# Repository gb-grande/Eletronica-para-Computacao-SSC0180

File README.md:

# SSC0180 - Eletrônica para Computação

Esse repo reúne os dois trabalhos desenvolvidos para a disciplina de Eletrônica para Computação - SSC0180, ministrada pelo professor Eduardo do Valle Simoes no ICMC.

Membros do grupo:

- Gustavo Bhering Grande - 12542780
- Joao Pedro Hamata - 13672001
- Lucas Oliveira Castro - 13695059
- Rafael de Almeida - 11872028

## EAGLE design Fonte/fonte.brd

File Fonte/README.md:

# FonteEletronica
Este trabalho, referente à disciplina Eletrônica para Computação(ICMC-USP), consiste no projeto e montagem de uma fonte de tensão ajustável entre 3V a 12V com capacidade de 100mA.

Adotou-se como parametros da entrada: Corrente alternada com 127V de tensao e 60Hz de frequencia.

| Apresentação da Fonte | Cálculo do Ripple |
| --- | --- |
| <video src="https://user-images.githubusercontent.com/24720405/178084118-f01fbc68-67f3-4e2c-8ba8-4f21347edacc.mp4" style="max-width: 730px;"></video> | <video src="https://user-images.githubusercontent.com/24720405/178084461-28b8bc12-fb25-4542-be41-ac9ad6f14883.mp4" style="max-width: 730px;"></video> |

| Componente | Preço |
| --- | --- |
| Transformador | R$28,99 |
| Diodo 1n4007 x4 | R$0,20 * 4 = R$0,80 |
| Capacitor 680uF 25v | R$5,78 |
| Resistor 1kΩ | R$0,07 |
| Resistor 750Ω | R$0,07 |
| Resistor 2k2Ω | R$0,07 |
| Potenciômetro Linear 5kΩ | R$7,00 |
| Diodo Zener 13v | R$0,48 |
| transistor NPN BC337-40 | R$0,69 |
| LED | R$0,50 |
| ***TOTAL*** | ***R$44,45*** |

*Componentes comprados na Ca&Ma em São Carlos, 28/06/2022

## Ficha Tecnica
### Transformador: 
Componente elétrico responsável por trasformar a tensão elétrica de entrada em valores mais adequados para uma determinada aplicação, utilizando-se de bobinas e dos princípios eletromagnéticos da Lei de Faraday-Lenz. No projeto, optou-se por um transformador comercial capaz de modificar uma entrada de 127V para aproximadamente 24v.
### Diodos:
Componentes eletricos com a caracteristica de selecionar um sentido unico para a passagem de corrente eletrica. No projeto, sao utilizados na construcao de uma ponte de diodos, dispositivo retificador de tensao por possibilitar o aproveitamento de ambos os ciclos da corrente alternada de origem.
### Resistores:
Componentes eletricos dotados de valores fixos de resistencia responsáveis por garantir a manutencao da corrente no circuito em valores adequados para o funcionamento adequado de cada um dos componentes presentes no circuito.
### Capacitor:
Componente elétrico capaz de armazenar pequenas quantidades de cargas elétricas, fornecendo corrente continua caso a tensão interna encontre-se superior à externa. Para obter um ripple inferior a 10%, seria necessário um capacitor de pelo menos 370uF (explicação no vídeo). No projeto, usamos um de 680uF.
### Potenciômetro:
Componente elétrico dotado de resistência variável, ou seja, capaz de regular a passagem de corrente e consequentemente modificar os valores de tensao do circuito. No projeto, foi utilizado para possibilitar a selecao dos valores de tensao entre 3V a 12V,  conforme descrito nas especificacoes.
### Diodo Zener:
Variacao do diodo tradicional caracterizado por permitir corrente eletrica somente sob a influencia de tensao superior a sua tensao de trabalho especificada pelo fabricante, limitando assim a voltagem maxima permitida pelo circuito. No projeto, foi utilizado para garantir valores de tensao maxima inferiores a 13V, com um espaço para erros do máximo de 12V.
### Transistor:
Componente elétrico capaz de trocar ou amplificar sinais e potencia eletrica. No projeto, foi utilizado na regulagem da corrente eletrica no circuito, para evitar desperdício de corrente no Diodo Zener.

## Funcionamento:
### Transformacao:
Nesta etapa, os sinais eletricos da entrada(corrente alternada com 127V de tensao e 60Hz de frequencia) tem sua DDP reduzida pelo transformador para valores proximos a 24V, sendo mantidas as demais caracteristicas de onda.
### Retificacao:
Nesta etapa, os sinais eletricos em corrente alternada(provenientes da etapa de transformacao) sao retificados para um sinal contiuamente positivo pela acao da ponte de diodos. Nesta estrutura, a disposicao geometrica dos diodos no circuito ora permite ora bloqueia a passagem de corrente eletrica, de modo a definir, durante ambos os ciclos da onda, um sentido unico para o fluxo de eletrons. O resultado do procedimento e uma reflexao completa dos valores negativos de tensao em relacao ao eixo das abcissas.
### Filtragem: 
Nesta etapa, os sinais eletricos arredondados pela caracteristica senoidal dos valores de entrada sao aproximados para valores continuos pela acao do capacitor eletrolitico. Tal estrutura, apos ser carregada brevemente durante os periodos de voltagem maxima, supre com libercao de corrente eletrica os momentos de diminuicao na voltagem de entrada, de modo a simular uma saida de tensao continua, sendo suas imperfeicoes parametrizadas pelo ripple.
### Regulagem:
Nesta etapa, os sinais eletricos ja trabalhados pelas etapas anteriores sao submentidos a uma maior establizacao e linearizacao em funcao da acao complementar entre o diodo Zener e o transistor, de modo que a saida do sistema configure uma tensao fixa e constante, a despeito de ligeiras imperfeicoes de processos anteriores ou mesmo da presenca de ruido por flutuacoes de corrente e temperatura. Finalmente, ativa-se o potenciometro para regular o valor de saida entre os especificados 3V e 12V.

[Circuito no Falstad](https://www.falstad.com/circuit/circuitjs.html?ctz=CQAgjCAMB0l3BWcA2aAOMB2ALGXyEw1sESQFJyRsBmcgUwFowwAoAN3DACYVKXe3NGijgQyfmkrSo0BKwDuXXmAngAnCrWRFykEJFhN+4VFYAVDYNMG+o7LKJpkmTSSE1ITkd2j512OoImGAI3DTIQtTQNK4INOpB6mjx2JCYTCyyieqsACYgNGF2aZTckD7gAHKl2PmFxdwIyNRw+hX61bX1ng7lIkVaZV1wdQW97QONzZ1gNaO6tqqUg3Y6SqWT1FJb6w2CM6u2e0c2ZyInkH0dE6uXDqvYO3esAE7k2H2YvKQPxWXlHQAY22ZQ6TxW-1k8BcOTh8MShTAMUg6gSIRo2G4mBouJaMDgbA2O36H2uF10EP2ZOpe1+WwkPg6OkxIAAXvQAHb0V7MOj8aAhWhhDCaDDwbhMTCiFT81hs8Q3cqKnw2dlcnl83SMwrKnUvJT64r0l6qH6fLb07GCEB5egAMwAhgBXAA2ABdGK76AUIDICWx3jrScGZmC4KwAOag6lU-CiPbBjqYYi7bUdJotFwHfGsd0gTDTFopvphsTMNAxQuQAyxb6EdSyIXCTCuIqYCrIZzgNp2p1u91vcTfanZ3UyQGJkerI28RPnAtFsyGjMzYOmHRYBxjzPD3g0ZUQChtAmQJAAJXoAGcAJZX92OzlA+i6EtbN-cNLLgup60-h5XGY7xvhMIFQjwexgbwY4vAA9g04gPK0iLKjAc7gKwQA)

Esquemático no EAGLE

Board no EAGLE

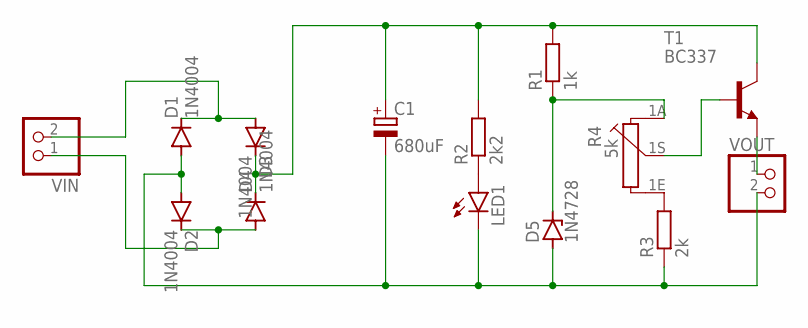
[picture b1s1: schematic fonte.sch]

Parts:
C1: 680uF; E5-10,5
D1, D2, D3, D4: 1N4004; DO41-10
D5: 1N4728; DO41Z10
LED1: LED5MM
R1: 1k; 0207/10
R2: 2k2; 0207/10
R3: 2k; 0207/10
R4: 5k; PC16S
T1: BC337; TO92
VIN: PINHD-1X2; 1X02
VOUT: PINHD-1X2; 1X02

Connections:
unnamed: C1.-, D1.A, D2.A, D5.A, LED1.K (C), R3.1, VOUT.2
unnamed: C1.+, D3.C, D4.C, R1.2, R2.2, T1.3 (C)
unnamed: LED1.A, R2.1
unnamed: D5.C, R1.1, R4.1A
unnamed: D1.C, D3.A, VIN.2
unnamed: D2.C, D4.A, VIN.1
unnamed: T1.1 (E), VOUT.1
unnamed: R3.2, R4.1E
unnamed: R4.1S, T1.2 (B)

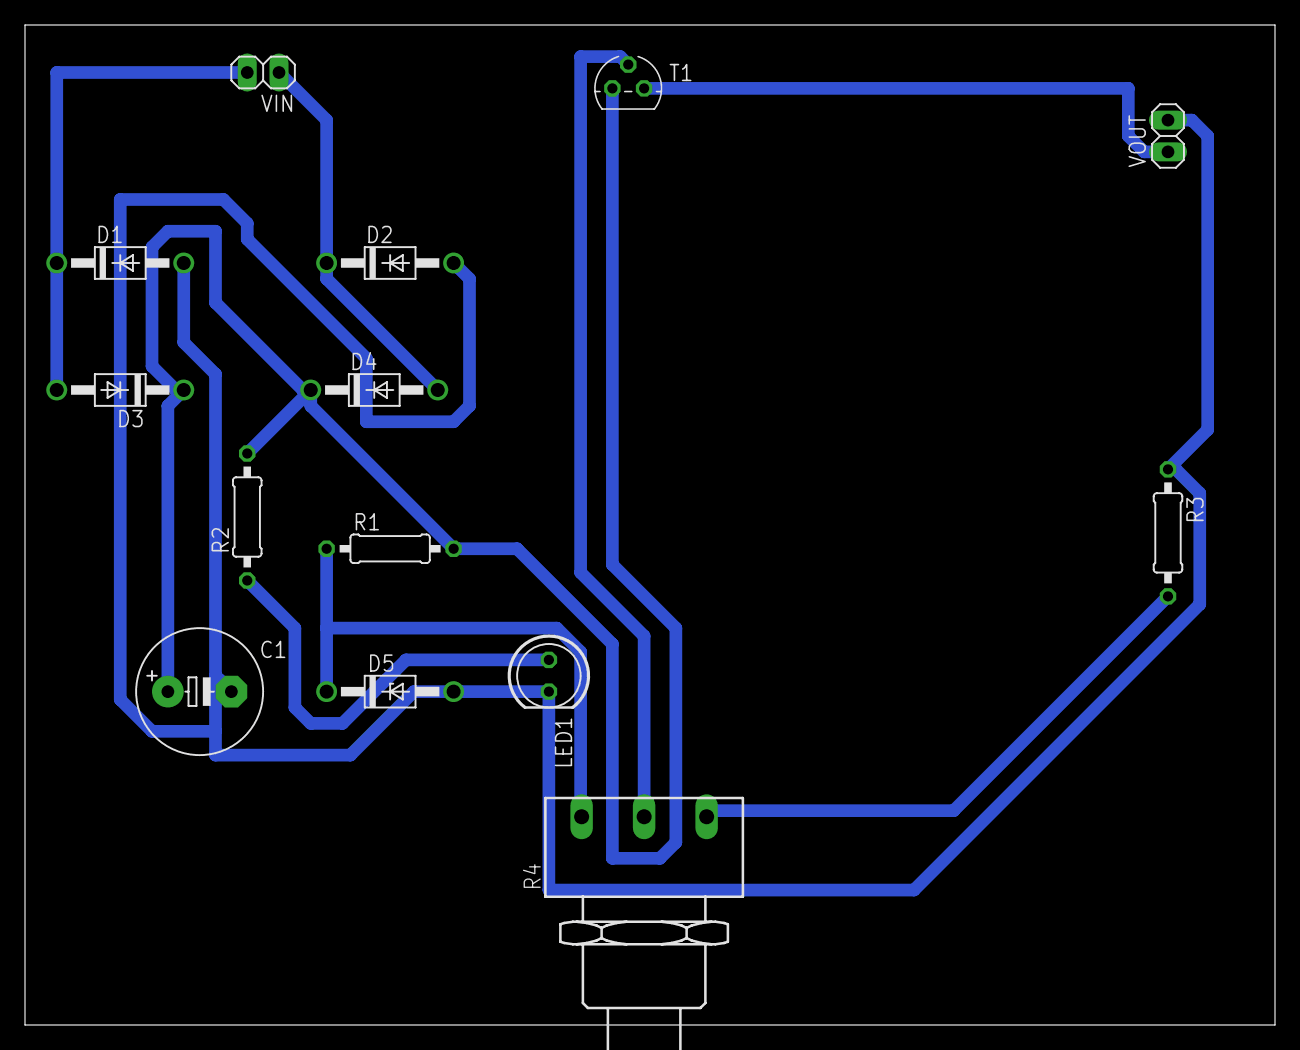
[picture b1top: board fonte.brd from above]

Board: 2 copper layers, 100.0 x 80.0 mm, 14 parts (0 on the bottom side), 9 nets.

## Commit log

2022-06-23 Circuito
2022-07-06 Adicionados esquemático e board do EAGLE
2022-07-09 Adiciona os vídeos
2022-07-09 Conserta o embed dos vídeos
2022-07-09 Atualiza o readme com o texto descritivo
2022-07-12 Organiza o repo para ficar de acordo com os mandamentos do Simões
2022-07-12 Termina de organizar o repo de acordo com as especificações do trabalho
2022-07-18 nomes em ordem alfabética e código da disciplina colocado
2022-07-18 Vídeo colocado
2022-07-19 Atualiza informação de resistores
2022-07-19 Atualiza alguns comentarios
2022-07-19 Muda local de compra de componentes e resistor
2022-07-19 Coloca link pro tinkercad do arduino
2022-07-20 prints atualizadas
2022-07-20 substituindo arquivos eagle
2022-07-20 quebra de linha
2022-07-23 Minor spelling mistake
